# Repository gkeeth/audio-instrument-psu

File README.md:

# Power Supply For Audio Instruments

Small power supply for powering DIY audio measurement instruments. Provides
+/- 12V via mini-DIN connectors.

## License
This work is licensed under a [Creative Commons Attribution-ShareAlike 4.0
International License][cc-by-sa].

[![CC BY-SA 4.0][cc-by-sa-image]][cc-by-sa]

[cc-by-sa]: http://creativecommons.org/licenses/by-sa/4.0/
[cc-by-sa-image]: https://licensebuttons.net/l/by-sa/4.0/88x31.png
[cc-by-sa-shield]: https://img.shields.io/badge/License-CC%20BY--SA%204.0-lightgrey.svg

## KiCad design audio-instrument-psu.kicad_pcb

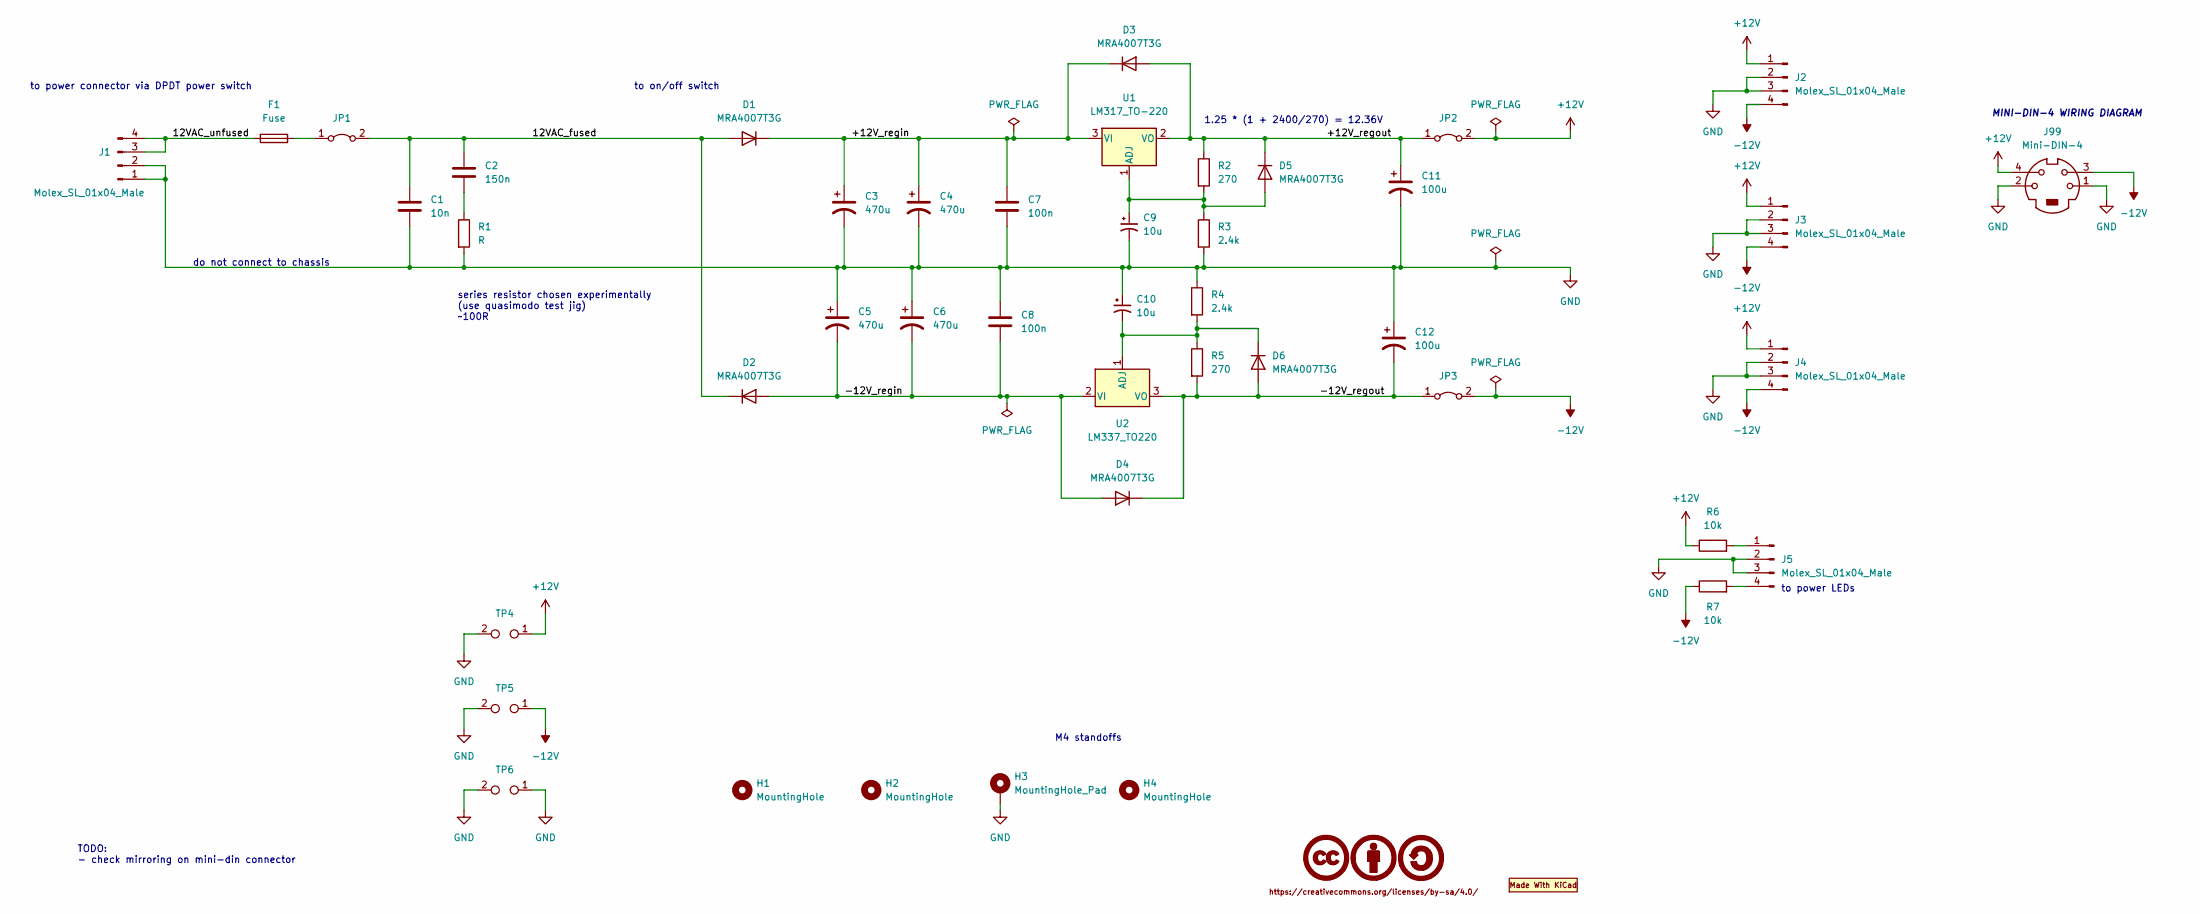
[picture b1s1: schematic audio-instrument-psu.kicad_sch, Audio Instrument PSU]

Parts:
C1: 10n; C_Rect_L7.2mm_W2.5mm_P5.00mm_FKS2_FKP2_MKS2_MKP2; Manufacturer PN B32529C3103J000
C2: 150n; C_Rect_L7.5mm_W6.5mm_P5.00mm; Manufacturer PN B32529C3154K000
C3, C4, C5, C6: 470u; CP_Radial_D10.0mm_P5.00mm; Voltage 35
C7, C8: 100n; C_0805_2012Metric
C9, C10: 10u; CP_Radial_D5.0mm_P2.50mm; Voltage 35V
C11, C12: 100u; CP_Radial_D6.3mm_P2.50mm; Voltage 35
D1, D2, D3, D4, D5, D6: MRA4007T3G; D_SMA
F1: Fuse; Fuseholder_Cylinder-5x20mm_Schurter_0031_8201_Horizontal_Op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
H1, H2, H4: MountingHole; MountingHole_4.3mm_M4
H3: MountingHole_Pad; MountingHole_4.3mm_M4_Pad
J1, J2, J3, J4, J5: Molex_SL_01x04_Male; Molex_SL_A-70543-0003_1x04_P2.54mm_Vertical
J99: Mini-DIN-4
JP1, JP2, JP3: Jumper_2_Bridged; PinHeader_1x02_P2.54mm_Vertical
LOGO1: CC-BY-SA_0.33in; CC-BY-SA_SilkScreenTop_Small
LOGO2: Logo_MadeWithKiCad; KiCad-Logo2_5mm_SilkScreen
R1: R; R_1206_3216Metric
R2, R5: 270; R_1206_3216Metric
R3, R4: 2.4k; R_1206_3216Metric
R6, R7: 10k; R_1206_3216Metric
TP4, TP5, TP6: TestPoint_2Pole; PinHeader_1x02_P2.54mm_Vertical
U1: LM317_TO-220; TO-220-3_Horizontal_TabUp
U2: LM337_TO220; TO-220-3_Horizontal_TabUp

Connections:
+12V: J2.1, J3.1, J4.1, J99.4, JP2.2 (B), R6.1, TP4.1
-12V: J2.4, J3.4, J4.4, J99.3, JP3.2 (B), R7.1, TP5.1
/12VAC_fused: C1.1, C2.1, D1.2 (A), D2.1 (K), JP1.2 (B)
/12VAC_unfused: F1.2, J1.3, J1.4
/+12V_regin: C3.1, C4.1, C7.1, D1.1 (K), D3.1 (K), U1.3 (VI)
/+12V_regout: C11.1, D3.2 (A), D5.1 (K), JP2.1 (A), R2.1, U1.2 (VO)
/-12V_regin: C5.2, C6.2, C8.2, D2.2 (A), D4.2 (A), U2.2 (VI)
/-12V_regout: C12.2, D4.1 (K), D6.2 (A), JP3.1 (A), R5.2, U2.3 (VO)
GND: C1.2, C3.2, C4.2, C5.1, C6.1, C7.2, C8.1, C9.2, C10.1, C11.2, C12.1, H3.1, J1.1, J1.2, J2.2, J2.3, J3.2, J3.3, J4.2, J4.3, J5.2, J5.3, J99.1, J99.2, R1.2, R3.2, R4.1, TP4.2, TP5.2, TP6.1, TP6.2
unnamed: C2.2, R1.1
unnamed: C9.1, D5.2 (A), R2.2, R3.1, U1.1 (ADJ)
unnamed: C10.2, D6.1 (K), R4.2, R5.1, U2.1 (ADJ)
unnamed: F1.1, JP1.1 (A)
unnamed: J5.1, R6.2
unnamed: J5.4, R7.2

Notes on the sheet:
to on/off switch
series resistor chosen experimentally (use quasimodo test jig) ~100R
to power LEDs
MINI-DIN-4 WIRING DIAGRAM
M4 standoffs
to power connector via DPDT power switch
do not connect to chassis
1.25 * (1 + 2400/270) = 12.36V
TODO: - check mirroring on mini-din connector

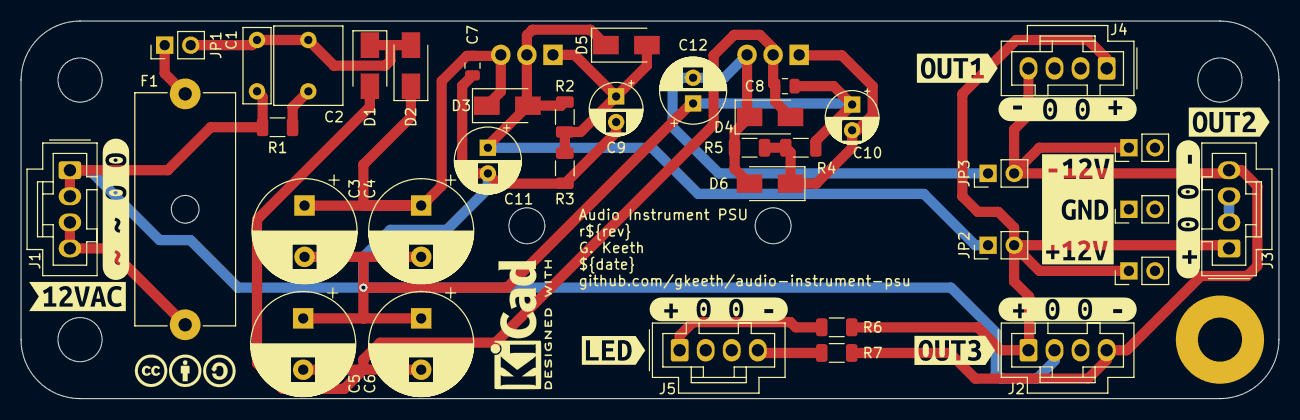
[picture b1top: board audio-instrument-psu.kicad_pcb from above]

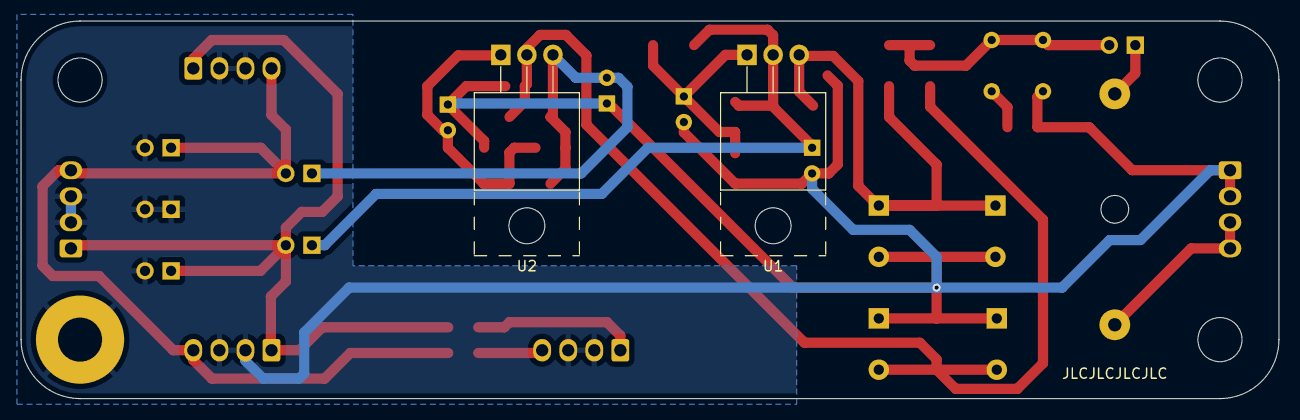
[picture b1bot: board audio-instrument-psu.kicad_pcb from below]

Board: 2 copper layers, 122.6 x 36.8 mm, 56 parts (2 on the bottom side), 15 nets.

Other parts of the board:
kibuzzard-6340BBAD, kibuzzard-6340BBAD#2, kibuzzard-6340BBAD#3, kibuzzard-6340BBAD#4: G***; kibuzzard-6340BBAD
kibuzzard-6340BC0E: G***; kibuzzard-6340BC0E
kibuzzard-6340BC06: G***; kibuzzard-6340BC06
kibuzzard-6340BC16: G***; kibuzzard-6340BC16
kibuzzard-6340BF5D: G***; kibuzzard-6340BF5D
kibuzzard-6340BF7A: G***; kibuzzard-6340BF7A
kibuzzard-6340BF8B: G***; kibuzzard-6340BF8B
kibuzzard-6340BFBC: G***; kibuzzard-6340BFBC

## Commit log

2022-09-08 add license/readme
2022-09-08 initial schematic complete
2022-09-08 update gitignore
2022-09-09 Working on TODO list
    - add mounting holes/brackets
    - add LED connector
    - add switch connector
    - add license/kicad decals
2022-09-13 add to TODO list
2022-09-13 Work through TODO list
    - add testpoints
    - simplify power switch connectors (wire directly from power connector
    to power switch, then power switch to board connector)
    - add caps on ADJ pins
    - add snubber
    - ERC clean
2022-09-14 remove redundant ADJ caps
2022-09-14 label nets
2022-09-14 initial placement complete
2022-09-14 initial routing complete, DRC clean
2022-09-21 ignore freecad backups
2022-09-21 add heatsink profile mechanical drawing
2022-10-03 change board to attach to heatsink mounting holes
2022-10-08 redo layout to mount onto heatsink directly
2022-10-08 ignore fab outputs
2022-10-08 update project date & DRC clean
2022-10-10 add power-din pinout to schematic
2022-12-29 add front panel

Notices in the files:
audio-instrument-psu.kicad_sch:
https://creativecommons.org/licenses/by-sa/4.0
